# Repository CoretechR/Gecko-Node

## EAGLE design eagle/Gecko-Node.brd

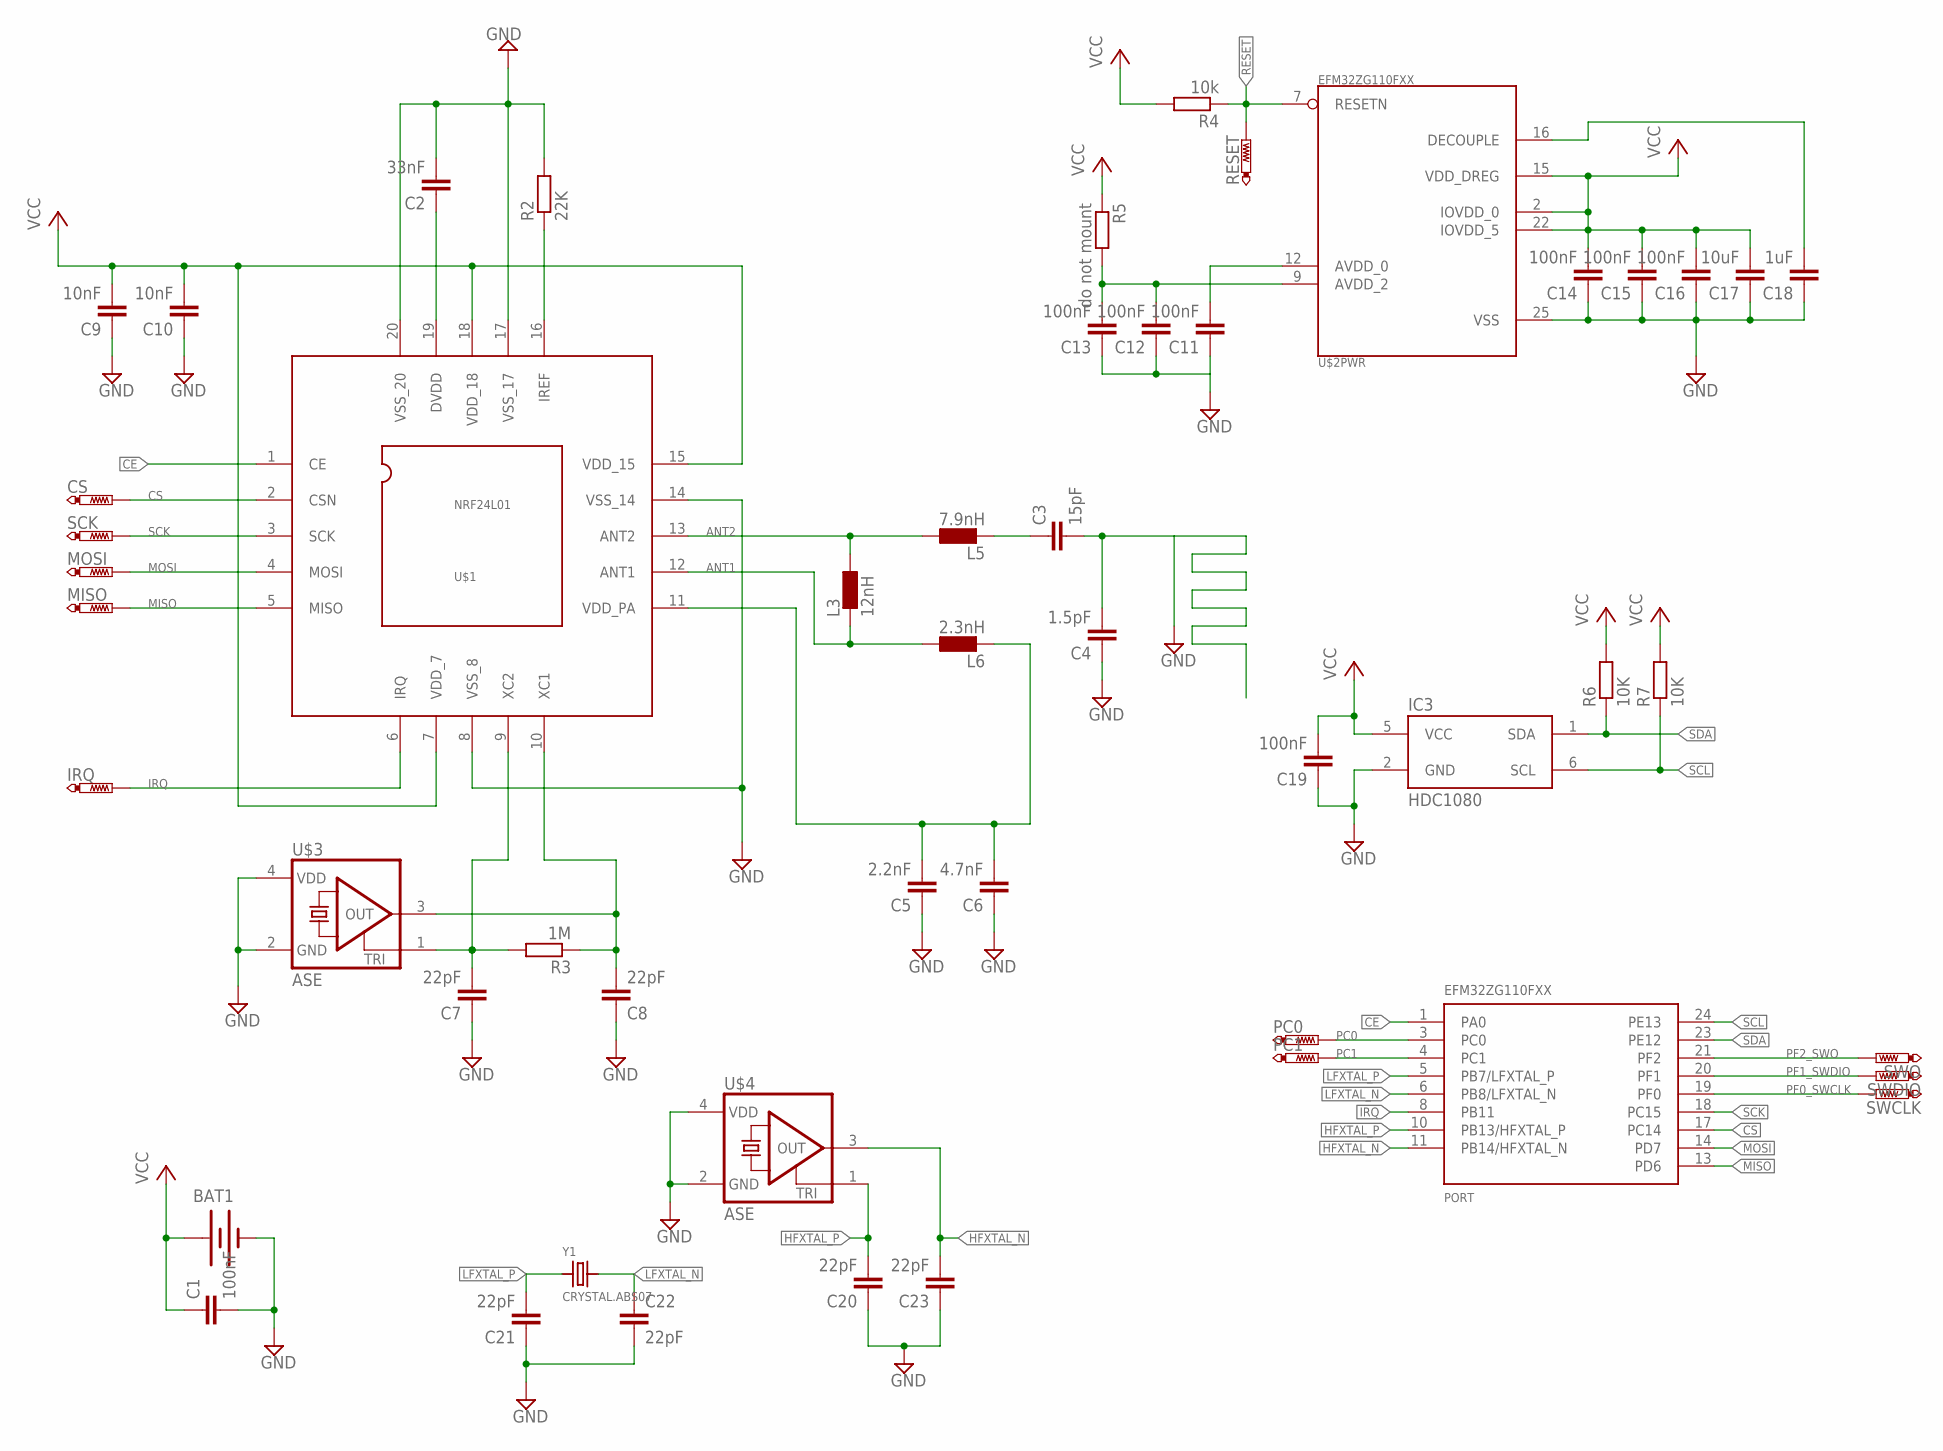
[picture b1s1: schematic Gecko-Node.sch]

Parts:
BAT1: LINX-BAT-HLD-00120SMD; BATTCON_20MM
C1, C11, C12, C13, C14, C15, C16, C19: 100nF; C0603
C2: 33nF; C0603
C3: 15pF; C0603
C4: 1.5pF; C0603
C5: 2.2nF; C0603
C6: 4.7nF; C0603
C7, C8, C20, C21, C22, C23: 22pF; C0603
C9, C10: 10nF; C0603
C17: 10uF; C0603
C18: 1uF; C0603
CS: PTR1TP08R; TP08R
IC3: HDC1080; WSON6
IRQ: PTR1TP08R; TP08R
L3: 12nH; R0603
L5: 7.9nH; R0603
L6: 2.3nH; R0603
MISO: PTR1TP08R; TP08R
MOSI: PTR1TP08R; TP08R
PC0, PC1: PTR1TP08R; TP08R
R2: 22K; R0603
R3: 1M; R0603
R4: 10k; R0603
R5: do not mount; R0603
R6, R7: 10K; R0603
RESET: PTR1TP08R; TP08R
SCK: PTR1TP08R; TP08R
SWCLK: PTR1TP08R; TP08R
SWDIO: PTR1TP08R; TP08R
SWO: PTR1TP08R; TP08R
U$1: NRF24L01; QFN20
U$2: EFM32ZG110FXX; QFN24
U$3, U$4: ASE
Y1: CRYSTAL.ABS07; ABS07

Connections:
ANT1: L3.2, L6.1, U$1.12 (ANT1)
ANT2: L3.1, L5.1, U$1.13 (ANT2)
CE: U$1.1 (CE), U$2.1 (PA0)
CS: CS.TP, U$1.2 (CSN), U$2.17 (PC14)
DECOUPLE: C18.2, U$2.16 (DECOUPLE)
GND: BAT1.2 (-), C1.2, C2.2, C3.2, C4.1, C4.2, C5.1, C6.1, C7.1, C8.1, C9.1, C10.1, C11.1, C12.1, C13.1, C14.1, C15.1, C16.1, C17.1, C18.1, C19.1, C20.1, C21.1, C22.2, C23.1, IC3.2 (GND), R2.2, U$1.8 (VSS_8), U$1.14 (VSS_14), U$1.17 (VSS_17), U$1.20 (VSS_20), U$2.25 (VSS), U$3.2 (GND), U$3.4 (VDD), U$4.2 (GND), U$4.4 (VDD)
HFXTAL_N: C23.2, U$2.11 (PB14/HFXTAL_N), U$4.3 (OUT)
HFXTAL_P: C20.2, U$2.10 (PB13/HFXTAL_P), U$4.1 (TRI)
IRQ: IRQ.TP, U$1.6 (IRQ), U$2.8 (PB11)
LFXTAL_N: C22.1, U$2.6 (PB8/LFXTAL_N), Y1.2
LFXTAL_P: C21.2, U$2.5 (PB7/LFXTAL_P), Y1.1
MISO: MISO.TP, U$1.5 (MISO), U$2.13 (PD6)
MOSI: MOSI.TP, U$1.4 (MOSI), U$2.14 (PD7)
unnamed: C7.2, R3.2, U$1.9 (XC2), U$3.1 (TRI)
unnamed: R2.1, U$1.16 (IREF)
unnamed: C2.1, U$1.19 (DVDD)
unnamed: C8.2, R3.1, U$1.10 (XC1), U$3.3 (OUT)
unnamed: C3.1, L5.2
unnamed: C11.2, U$2.12 (AVDD_0)
unnamed: C5.2, C6.2, L6.2, U$1.11 (VDD_PA)
unnamed: C12.2, C13.2, R5.2, U$2.9 (AVDD_2)
PC0: PC0.TP, U$2.3 (PC0)
PC1: PC1.TP, U$2.4 (PC1)
PF0_SWCLK: SWCLK.TP, U$2.19 (PF0)
PF1_SWDIO: SWDIO.TP, U$2.20 (PF1)
PF2_SWO: SWO.TP, U$2.21 (PF2)
RESET: R4.1, RESET.TP, U$2.7 (RESETN)
SCK: SCK.TP, U$1.3 (SCK), U$2.18 (PC15)
SCL: IC3.6 (SCL), R7.1, U$2.24 (PE13)
SDA: IC3.1 (SDA), R6.1, U$2.23 (PE12)
VCC: BAT1.1 (+), BAT1.3 (+), C1.1, C9.2, C10.2, C14.2, C15.2, C16.2, C17.2, C19.2, IC3.5 (VCC), R4.2, R5.1, R6.2, R7.2, U$1.7 (VDD_7), U$1.15 (VDD_15), U$1.18 (VDD_18), U$2.2 (IOVDD_0), U$2.15 (VDD_DREG), U$2.22 (IOVDD_5)

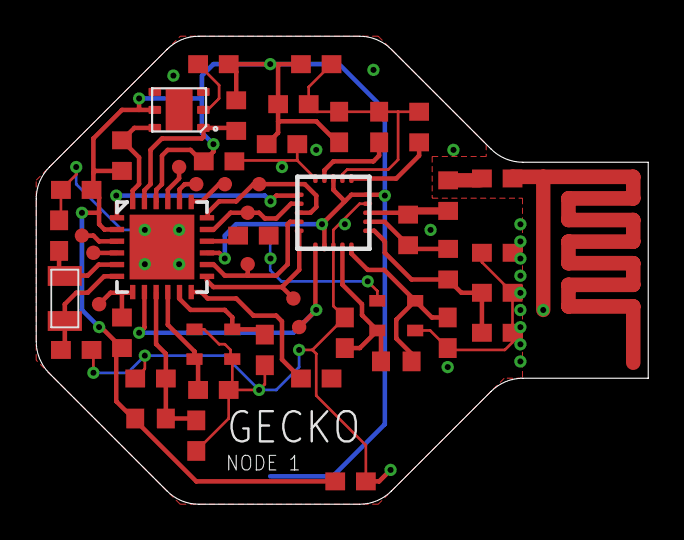
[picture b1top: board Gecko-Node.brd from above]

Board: 2 copper layers, 34.0 x 26.0 mm, 50 parts (1 on the bottom side), 31 nets.

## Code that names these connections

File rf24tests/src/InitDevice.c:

// $[Library includes]
#include "em_system.h"
#include "em_emu.h"
#include "em_cmu.h"
#include "em_device.h"
#include "em_chip.h"
#include "em_assert.h"
#include "em_gpio.h"
#include "em_i2c.h"
#include "em_rtc.h"
#include "em_usart.h"
// [Library includes]$

extern void enter_DefaultMode_from_RESET(void) {
	// $[Config Calls]
	HFXO_enter_DefaultMode_from_RESET();
	LFXO_enter_DefaultMode_from_RESET();
	CMU_enter_DefaultMode_from_RESET();
	RTC_enter_DefaultMode_from_RESET();
	USART1_enter_DefaultMode_from_RESET();
	I2C0_enter_DefaultMode_from_RESET();
	PORTIO_enter_DefaultMode_from_RESET();
	// [Config Calls]$
}

extern void HFXO_enter_DefaultMode_from_RESET(void) {

	// $[HFXO]
	CMU->CTRL = (CMU->CTRL & ~_CMU_CTRL_HFXOMODE_MASK) | CMU_CTRL_HFXOMODE_XTAL;

	CMU->CTRL = (CMU->CTRL & ~_CMU_CTRL_HFXOBOOST_MASK)
			| CMU_CTRL_HFXOBOOST_50PCENT;

	SystemHFXOClockSet(32000000);
	// [HFXO]$

}

extern void LFXO_enter_DefaultMode_from_RESET(void) {

	// $[Use oscillator source]
	CMU->CTRL = (CMU->CTRL & ~_CMU_CTRL_LFXOMODE_MASK) | CMU_CTRL_LFXOMODE_XTAL;
	// [Use oscillator source]$

	// $[LFXO Boost Percent]
	CMU->CTRL = (CMU->CTRL & ~_CMU_CTRL_LFXOBOOST_MASK)
			| CMU_CTRL_LFXOBOOST_100PCENT;
	// [LFXO Boost Percent]$

	// $[REDLFXO Boost]
	// [REDLFXO Boost]$

}

extern void CMU_enter_DefaultMode_from_RESET(void) {

	// $[LFXO enable]
	CMU_OscillatorEnable(cmuOsc_LFXO, true, true);
	// [LFXO enable]$

	// $[HFXO enable]
	CMU_OscillatorEnable(cmuOsc_HFXO, true, true);
	// [HFXO enable]$

	// $[LFACLK Setup]
	/* Select LFXO as clock source for LFACLK */
	CMU_ClockSelectSet(cmuClock_LFA, cmuSelect_LFXO);

	// [LFACLK Setup]$

	// $[High Frequency Clock select]
	/* Using HFXO as high frequency clock, HFCLK */
	CMU_ClockSelectSet(cmuClock_HF, cmuSelect_HFXO);

	/* Enable peripheral clock */
	CMU_ClockEnable(cmuClock_HFPER, true);

	// [High Frequency Clock select]$

	// $[LF clock tree setup]
	/* Enable LF clocks */
	CMU_ClockEnable(cmuClock_CORELE, true);
	CMU_ClockSelectSet(cmuClock_LFA, cmuSelect_LFXO);
	// [LF clock tree setup]$
	// $[Peripheral Clock enables]
	/* Enable clock for I2C0 */
	CMU_ClockEnable(cmuClock_I2C0, true);

	/* Enable clock for RTC */
	CMU_ClockEnable(cmuClock_RTC, true);

	/* Enable clock for USART1 */
	CMU_ClockEnable(cmuClock_USART1, true);

	/* Enable clock for GPIO by default */
	CMU_ClockEnable(cmuClock_GPIO, true);

	// [Peripheral Clock enables]$

}

extern void ADC0_enter_DefaultMode_from_RESET(void) {

	// $[ADC_Init]
	// [ADC_Init]$

	// $[ADC_InitSingle]
	// [ADC_InitSingle]$

	// $[ADC_InitScan]
	// [ADC_InitScan]$

}

extern void ACMP0_enter_DefaultMode_from_RESET(void) {

	// $[ACMP Initialization]
	// [ACMP Initialization]$

	// $[ACMP Channel config]
	// [ACMP Channel config]$

}

extern void IDAC0_enter_DefaultMode_from_RESET(void) {

	// $[IDAC Initialization]
	// [IDAC Initialization]$

	// $[IDAC optional configurations]
	// [IDAC optional configurations]$

	// $[IDAC enable]
	// [IDAC enable]$

}

extern void RTC_enter_DefaultMode_from_RESET(void) {

	// $[RTC_Init]
	RTC_Init_TypeDef init = RTC_INIT_DEFAULT;

	init.debugRun = 0;
	init.comp0Top = 0;

	RTC_Init(&init);
	// [RTC_Init]$

}

extern void USART1_enter_DefaultMode_from_RESET(void) {

	// $[USART_InitAsync]
	// [USART_InitAsync]$

	// $[USART_InitSync]
	USART_InitSync_TypeDef initsync = USART_INITSYNC_DEFAULT;

	initsync.baudrate = 1200000;
	initsync.databits = usartDatabits8;
	initsync.master = 1;
	initsync.msbf = 1;
	initsync.clockMode = usartClockMode0;
#if defined( USART_INPUT_RXPRS ) && defined( USART_TRIGCTRL_AUTOTXTEN )
	initsync.prsRxEnable = 0;
	initsync.prsRxCh = 0;
	initsync.autoTx = 0;
#endif

	USART_InitSync(USART1, &initsync);
	// [USART_InitSync]$

	// $[USART_InitPrsTrigger]
	USART_PrsTriggerInit_TypeDef initprs = USART_INITPRSTRIGGER_DEFAULT;

	initprs.rxTriggerEnable = 0;
	initprs.txTriggerEnable = 0;
	initprs.prsTriggerChannel = usartPrsTriggerCh0;

	USART_InitPrsTrigger(USART1, &initprs);
	// [USART_InitPrsTrigger]$

}

extern void LEUART0_enter_DefaultMode_from_RESET(void) {

	// $[LEUART0 initialization]
	// [LEUART0 initialization]$

}

extern void VCMP_enter_DefaultMode_from_RESET(void) {

	// $[VCMP_Init]
	// [VCMP_Init]$

}

extern void WDOG_enter_DefaultMode_from_RESET(void) {

	// $[CMU_ClockEnable]
	// [CMU_ClockEnable]$

	// $[CMU_OscillatorEnable]
	// [CMU_OscillatorEnable]$

	// $[WDOG_Init]
	// [WDOG_Init]$

}

extern void I2C0_enter_DefaultMode_from_RESET(void) {

	// $[I2C0 initialization]
	I2C_Init_TypeDef init = I2C_INIT_DEFAULT;

	init.enable = 1;
	init.master = 1;
	init.freq = I2C_FREQ_FAST_MAX;
	init.clhr = i2cClockHLRAsymetric;
	I2C_Init(I2C0, &init);
	// [I2C0 initialization]$

}

extern void TIMER0_enter_DefaultMode_from_RESET(void) {

	// $[TIMER0 initialization]
	// [TIMER0 initialization]$

	// $[TIMER0 CC0 init]
	// [TIMER0 CC0 init]$

	// $[TIMER0 CC1 init]
	// [TIMER0 CC1 init]$

	// $[TIMER0 CC2 init]
	// [TIMER0 CC2 init]$

}

extern void TIMER1_enter_DefaultMode_from_RESET(void) {

	// $[TIMER1 initialization]
	// [TIMER1 initialization]$

	// $[TIMER1 CC0 init]
	// [TIMER1 CC0 init]$

	// $[TIMER1 CC1 init]
	// [TIMER1 CC1 init]$

	// $[TIMER1 CC2 init]
	// [TIMER1 CC2 init]$

}

extern void PCNT0_enter_DefaultMode_from_RESET(void) {

	// $[PCNT0 initialization]
	// [PCNT0 initialization]$

}

extern void PRS_enter_DefaultMode_from_RESET(void) {

	// $[PRS initialization]
	// [PRS initialization]$

}

extern void PORTIO_enter_DefaultMode_from_RESET(void) {

	// $[Port A Configuration]

	/* Pin PA0 is configured to Push-pull */
	GPIO->P[0].MODEL = (GPIO->P[0].MODEL & ~_GPIO_P_MODEL_MODE0_MASK)
			| GPIO_P_MODEL_MODE0_PUSHPULL;
	// [Port A Configuration]$

	// $[Port B Configuration]
	// [Port B Configuration]$

	// $[Port C Configuration]

	/* Pin PC8 is configured to Input enabled with filter */
	GPIO->P[2].DOUT |= (1 << 8);
	GPIO->P[2].MODEH = (GPIO->P[2].MODEH & ~_GPIO_P_MODEH_MODE8_MASK)
			| GPIO_P_MODEH_MODE8_INPUT;

	/* Pin PC9 is configured to Input enabled with filter */
	GPIO->P[2].DOUT |= (1 << 9);
	GPIO->P[2].MODEH = (GPIO->P[2].MODEH & ~_GPIO_P_MODEH_MODE9_MASK)
			| GPIO_P_MODEH_MODE9_INPUT;

	/* Pin PC10 is configured to Push-pull */
	GPIO->P[2].MODEH = (GPIO->P[2].MODEH & ~_GPIO_P_MODEH_MODE10_MASK)
			| GPIO_P_MODEH_MODE10_PUSHPULL;

	/* Pin PC11 is configured to Push-pull */
	GPIO->P[2].MODEH = (GPIO->P[2].MODEH & ~_GPIO_P_MODEH_MODE11_MASK)
			| GPIO_P_MODEH_MODE11_PUSHPULL;

	/* Pin PC14 is configured to Push-pull */
	GPIO->P[2].MODEH = (GPIO->P[2].MODEH & ~_GPIO_P_MODEH_MODE14_MASK)
			| GPIO_P_MODEH_MODE14_PUSHPULL;

	/* Pin PC15 is configured to Push-pull */
	GPIO->P[2].MODEH = (GPIO->P[2].MODEH & ~_GPIO_P_MODEH_MODE15_MASK)
			| GPIO_P_MODEH_MODE15_PUSHPULL;
	// [Port C Configuration]$

	// $[Port D Configuration]

	/* Pin PD6 is configured to Input enabled */
	GPIO->P[3].MODEL = (GPIO->P[3].MODEL & ~_GPIO_P_MODEL_MODE6_MASK)
			| GPIO_P_MODEL_MODE6_INPUT;

	/* Pin PD7 is configured to Push-pull */
	GPIO->P[3].MODEL = (GPIO->P[3].MODEL & ~_GPIO_P_MODEL_MODE7_MASK)
			| GPIO_P_MODEL_MODE7_PUSHPULL;
	// [Port D Configuration]$

	// $[Port E Configuration]

	/* Pin PE12 is configured to Open-drain with pull-up and filter */
	GPIO->P[4].MODEH = (GPIO->P[4].MODEH & ~_GPIO_P_MODEH_MODE12_MASK)
			| GPIO_P_MODEH_MODE12_WIREDANDPULLUPFILTER;

	/* Pin PE13 is configured to Open-drain with pull-up and filter */
	GPIO->P[4].MODEH = (GPIO->P[4].MODEH & ~_GPIO_P_MODEH_MODE13_MASK)
			| GPIO_P_MODEH_MODE13_WIREDANDPULLUPFILTER;
	// [Port E Configuration]$

	// $[Port F Configuration]
	// [Port F Configuration]$

	// $[Route Configuration]

	/* Module I2C0 is configured to location 6 */
	I2C0->ROUTE = (I2C0->ROUTE & ~_I2C_ROUTE_LOCATION_MASK)
			| I2C_ROUTE_LOCATION_LOC6;

	/* Enable signals SCL, SDA */
	I2C0->ROUTE |= I2C_ROUTE_SCLPEN | I2C_ROUTE_SDAPEN;

	/* Module USART1 is configured to location 3 */
	USART1->ROUTE = (USART1->ROUTE & ~_USART_ROUTE_LOCATION_MASK)
			| USART_ROUTE_LOCATION_LOC3;

	/* Enable signals CLK, RX, TX */
	USART1->ROUTE |= USART_ROUTE_CLKPEN | USART_ROUTE_RXPEN | USART_ROUTE_TXPEN;
	// [Route Configuration]$

}
